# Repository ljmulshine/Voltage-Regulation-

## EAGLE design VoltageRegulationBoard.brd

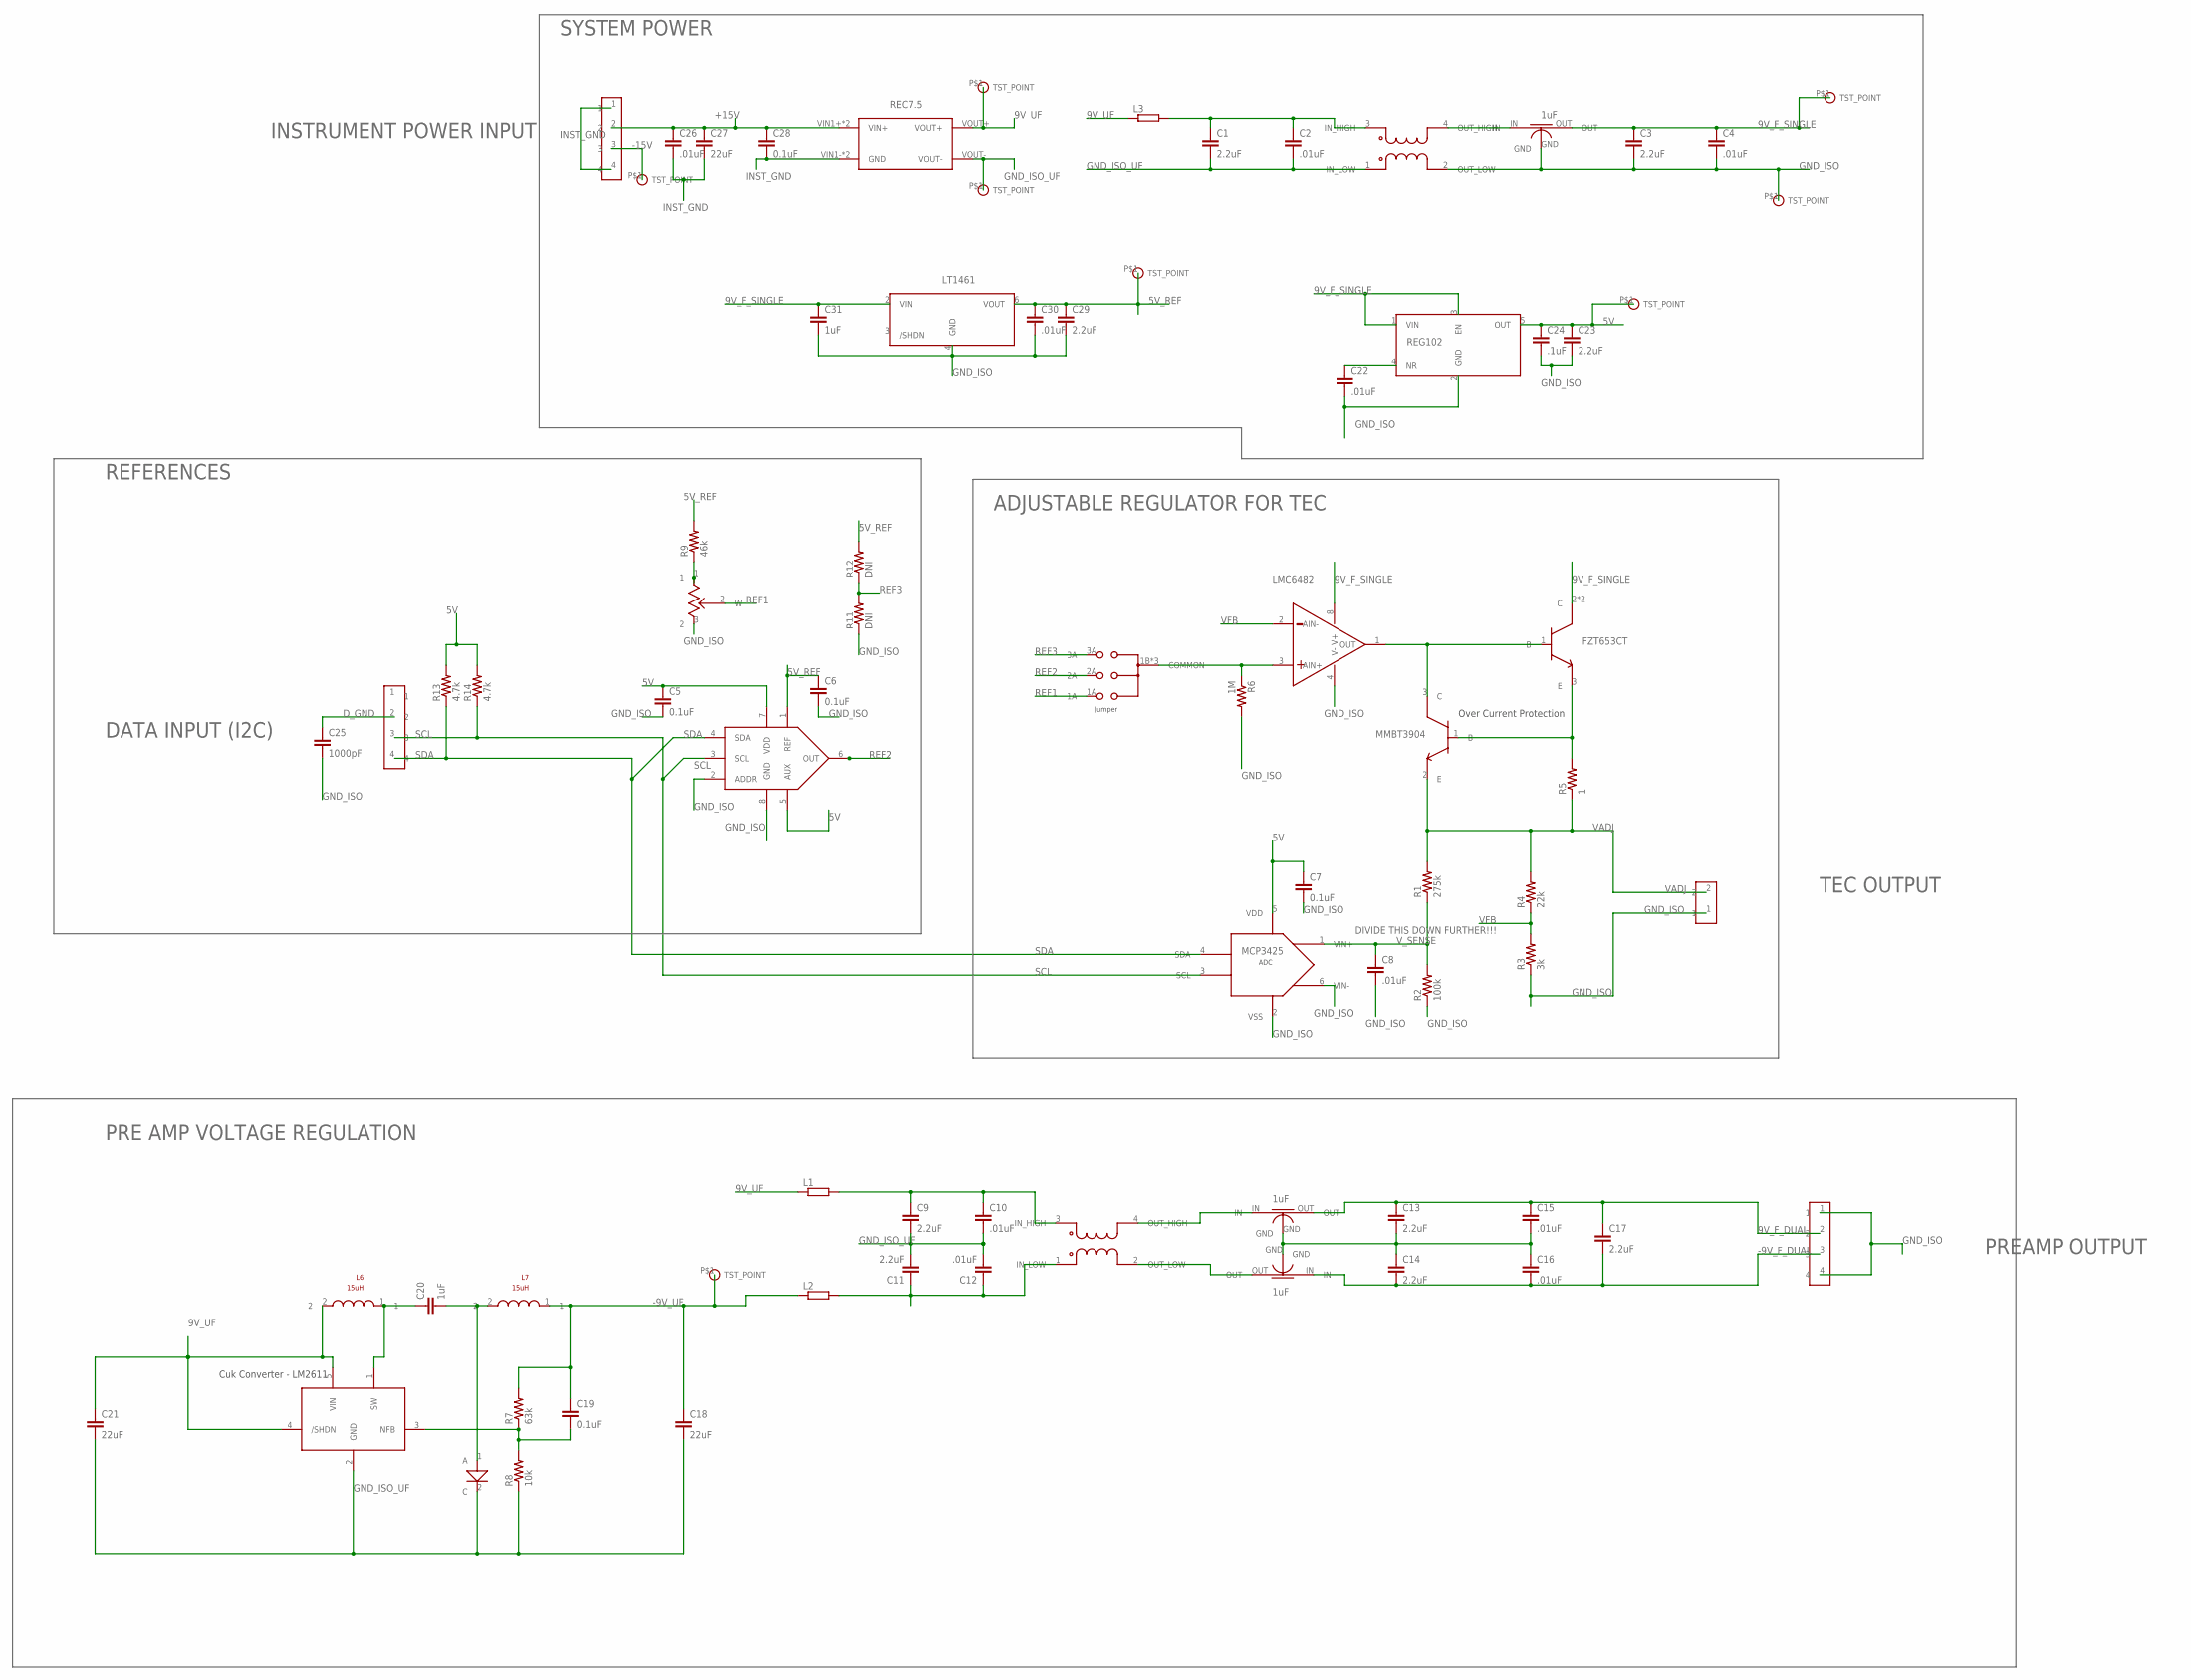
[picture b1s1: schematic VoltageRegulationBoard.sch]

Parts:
5V, 9V_F_S, 9V_UF: TST_PT; TST_POINT
-9V_U, -15V: TST_PT; TST_POINT
C1, C3, C9, C11, C13, C14, C17, C23, C29: 2.2uF; C0603
C2, C4, C8, C10, C12, C15, C16, C22, C26, C30: .01uF; C0603
C5, C6, C7, C19, C28: 0.1uF; C0603
C18, C21, C27: 22uF; C1206
C20, C31: 1uF; C0603
C24: .1uF; C0603
C25: 1000pF; C0603
FC1, FC2, FC3: FEED_THRU_CAP; 3-TERM-CAP
GND_ISO: TST_PT; TST_POINT
GND_ISO_UF: TST_PT; TST_POINT
J1, J2, J3: 4-OUT; 4-THRU
J4: 2-THRU; 2-THRU-.1
L1, L2, L3: R-EU_R0603; R0603
L4, L5: COMMON_MODE_CHOKE; COMM_MODE_CHOKE
L6, L7: 15uH; INDUCTOR_FOOTPRNT
R1: 275k; R0603
R2: 100k; R0603
R3: 3k; R0603
R4: 22k; R0603
R5: 1; R2512
R6: 1M; R0603
R7: 63k; R0603
R8: 10k; R0603
R9: 46k; R0603
R10: POTENTIOMETER; 3-THRU
R11, R12: DNI; R0603
R13, R14: 4.7k; R0603
T1: MMBT3904LT1GOSCT-ND(SMALL-SIGNAL-NMOS); SOT23
T2: FZT653-NPNBJT; SOT223
U1: LMC6482; SOIC8
U2: DAC_UMAX; 8-UMAX
U3: VREF; SOIC8
U4: REC7.5-1209
U5: REG102; SOT-23-5
U6: MCP3425A0T-E; SOT-23-6
U7: LM2611; SOT-23-5
U$3: 3XJUMPER; 2-THRU
U$10: SCHOTTKY; SOD-123
VREF: TST_PT; TST_POINT

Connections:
5V: 5V.P$1, C5.1, C7.1, C23.1, C24.1, R13.2, R14.2, U2.5 (AUX), U2.7 (VDD), U5.5 (OUT), U6.5 (VDD)
5V_REF: C6.1, C29.1, C30.1, R9.2, R12.2, U2.1 (REF), U3.6 (VOUT), VREF.P$1
9V_F_DUAL: C13.1, C15.1, C17.1, FC2.OUT, J2.2
9V_F_SINGLE: 9V_F_S.P$1, C3.1, C4.1, C31.1, FC3.OUT, T2.2 (C), T2.4 (C), U1.8 (V+), U3.2 (VIN), U5.1 (VIN), U5.3 (EN)
9V_UF: 9V_UF.P$1, C21.1, L1.1, L3.1, L6.2, U4.VOUT+, U7.4 (/SHDN), U7.5 (VIN)
9V_UF1: C1.1, C2.1, L3.2, L5.3 (IN_HIGH)
+15V: C26.1, C27.1, C28.1, J1.2, U4.VIN1+ (VIN+), U4.VIN2+ (VIN+)
-9V_F_DUAL: C14.2, C16.2, C17.2, FC1.IN, J2.3
-9V_UF: -9V_U.P$1, C18.1, C19.1, L2.1, L7.1, R7.2
-15V: -15V.P$1, J1.3
D_GND: C25.1, J3.2
GND_ISO: C3.2, C4.2, C5.2, C6.2, C7.2, C8.2, C13.2, C14.1, C15.2, C16.1, C22.2, C23.2, C24.2, C25.2, C29.2, C30.2, C31.2, FC1.GND, FC2.GND, FC3.GND, GND_ISO.P$1, J2.1, J2.4, J4.1, L5.2 (OUT_LOW), R2.1, R3.1, R6.2, R10.3 (2), R11.1, U1.4 (V-), U2.2 (ADDR), U2.8 (GND), U3.4 (GND), U5.2 (GND), U6.2 (VSS), U6.6 (VIN-)
GND_ISO_UF: C1.2, C2.2, C9.2, C10.2, C11.2, C12.2, C18.2, C21.2, GND_ISO_UF.P$1, L5.1 (IN_LOW), R8.1, U4.VOUT-, U7.2 (GND), U$10.2 (C)
INST_GND: C26.2, C27.2, C28.2, J1.1, J1.4, U4.VIN1- (GND), U4.VIN2- (GND)
unnamed: T1.3 (C), T2.1 (B), U1.1 (OUT)
unnamed: R9.1, R10.1
unnamed: R5.2, T1.1 (B), T2.3 (E)
unnamed: C22.1, U5.4 (NR)
unnamed: C9.1, C10.1, L1.2, L4.3 (IN_HIGH)
unnamed: C19.2, R7.1, R8.2, U7.3 (NFB)
unnamed: C20.1, L6.1, U7.1 (SW)
unnamed: FC2.IN, L4.4 (OUT_HIGH)
unnamed: FC1.OUT, L4.2 (OUT_LOW)
unnamed: C20.2, L7.2, U$10.1 (A)
unnamed: C11.1, C12.1, L2.2, L4.1 (IN_LOW)
unnamed: FC3.IN, L5.4 (OUT_HIGH)
unnamed: R6.1, U1.3 (AIN+), U$3.1B (COMMON), U$3.2B (COMMON), U$3.3B (COMMON)
REF1: R10.2 (W), U$3.1A
REF2: U2.6 (OUT), U$3.2A
REF3: R11.2, R12.1, U$3.3A
SCL: J3.3, R14.1, U2.3 (SCL), U6.3 (SCL)
SDA: J3.4, R13.1, U2.4 (SDA), U6.4 (SDA)
VADJ: J4.2, R1.2, R4.2, R5.1, T1.2 (E)
VFB: R3.2, R4.1, U1.2 (AIN-)
V_SENSE: C8.1, R1.1, R2.2, U6.1 (VIN+)

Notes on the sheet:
Over Current Protection
1uF
DIVIDE THIS DOWN FURTHER!!!
REC7.5
REG102
LT1461
LMC6482
FZT653CT
MMBT3904
MCP3425
REFERENCES
ADJUSTABLE REGULATOR FOR TEC
SYSTEM POWER
PRE AMP VOLTAGE REGULATION
TEC OUTPUT
PREAMP OUTPUT
DATA INPUT (I2C)
INSTRUMENT POWER INPUT

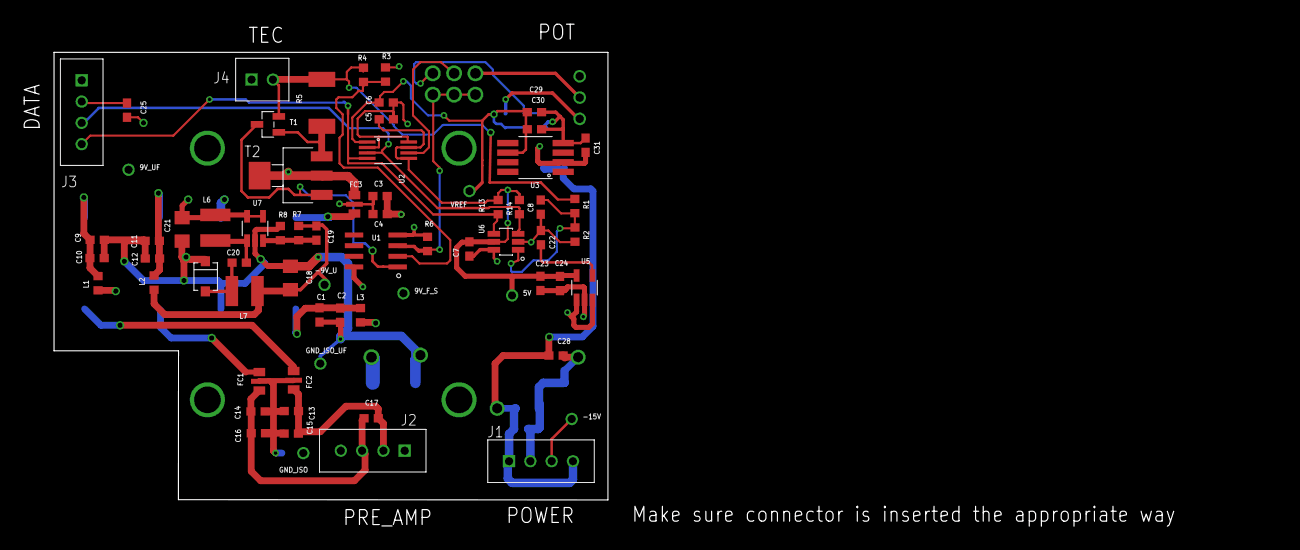
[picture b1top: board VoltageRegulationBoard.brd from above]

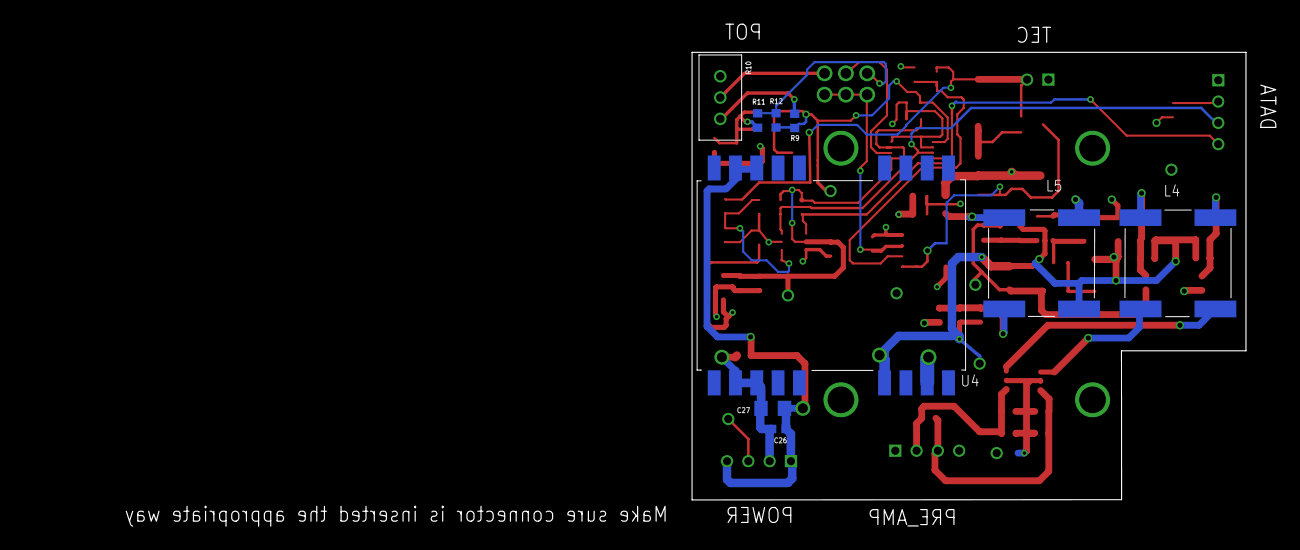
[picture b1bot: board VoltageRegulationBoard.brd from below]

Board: 4 copper layers, 151.0 x 61.6 mm, 79 parts (9 on the bottom side), 35 nets.

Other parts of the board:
DRILEGEND: DRILEGEND

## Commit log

2017-04-02 Placed Isolated switchin regulator on board
2017-04-02 Adding schematic, board and library files
2017-04-19 layout and schematic complete. Ready for final review
2017-04-22 Layout mostly complete. Making finishing documentation touches:
2017-04-24 altered LM6482 part
